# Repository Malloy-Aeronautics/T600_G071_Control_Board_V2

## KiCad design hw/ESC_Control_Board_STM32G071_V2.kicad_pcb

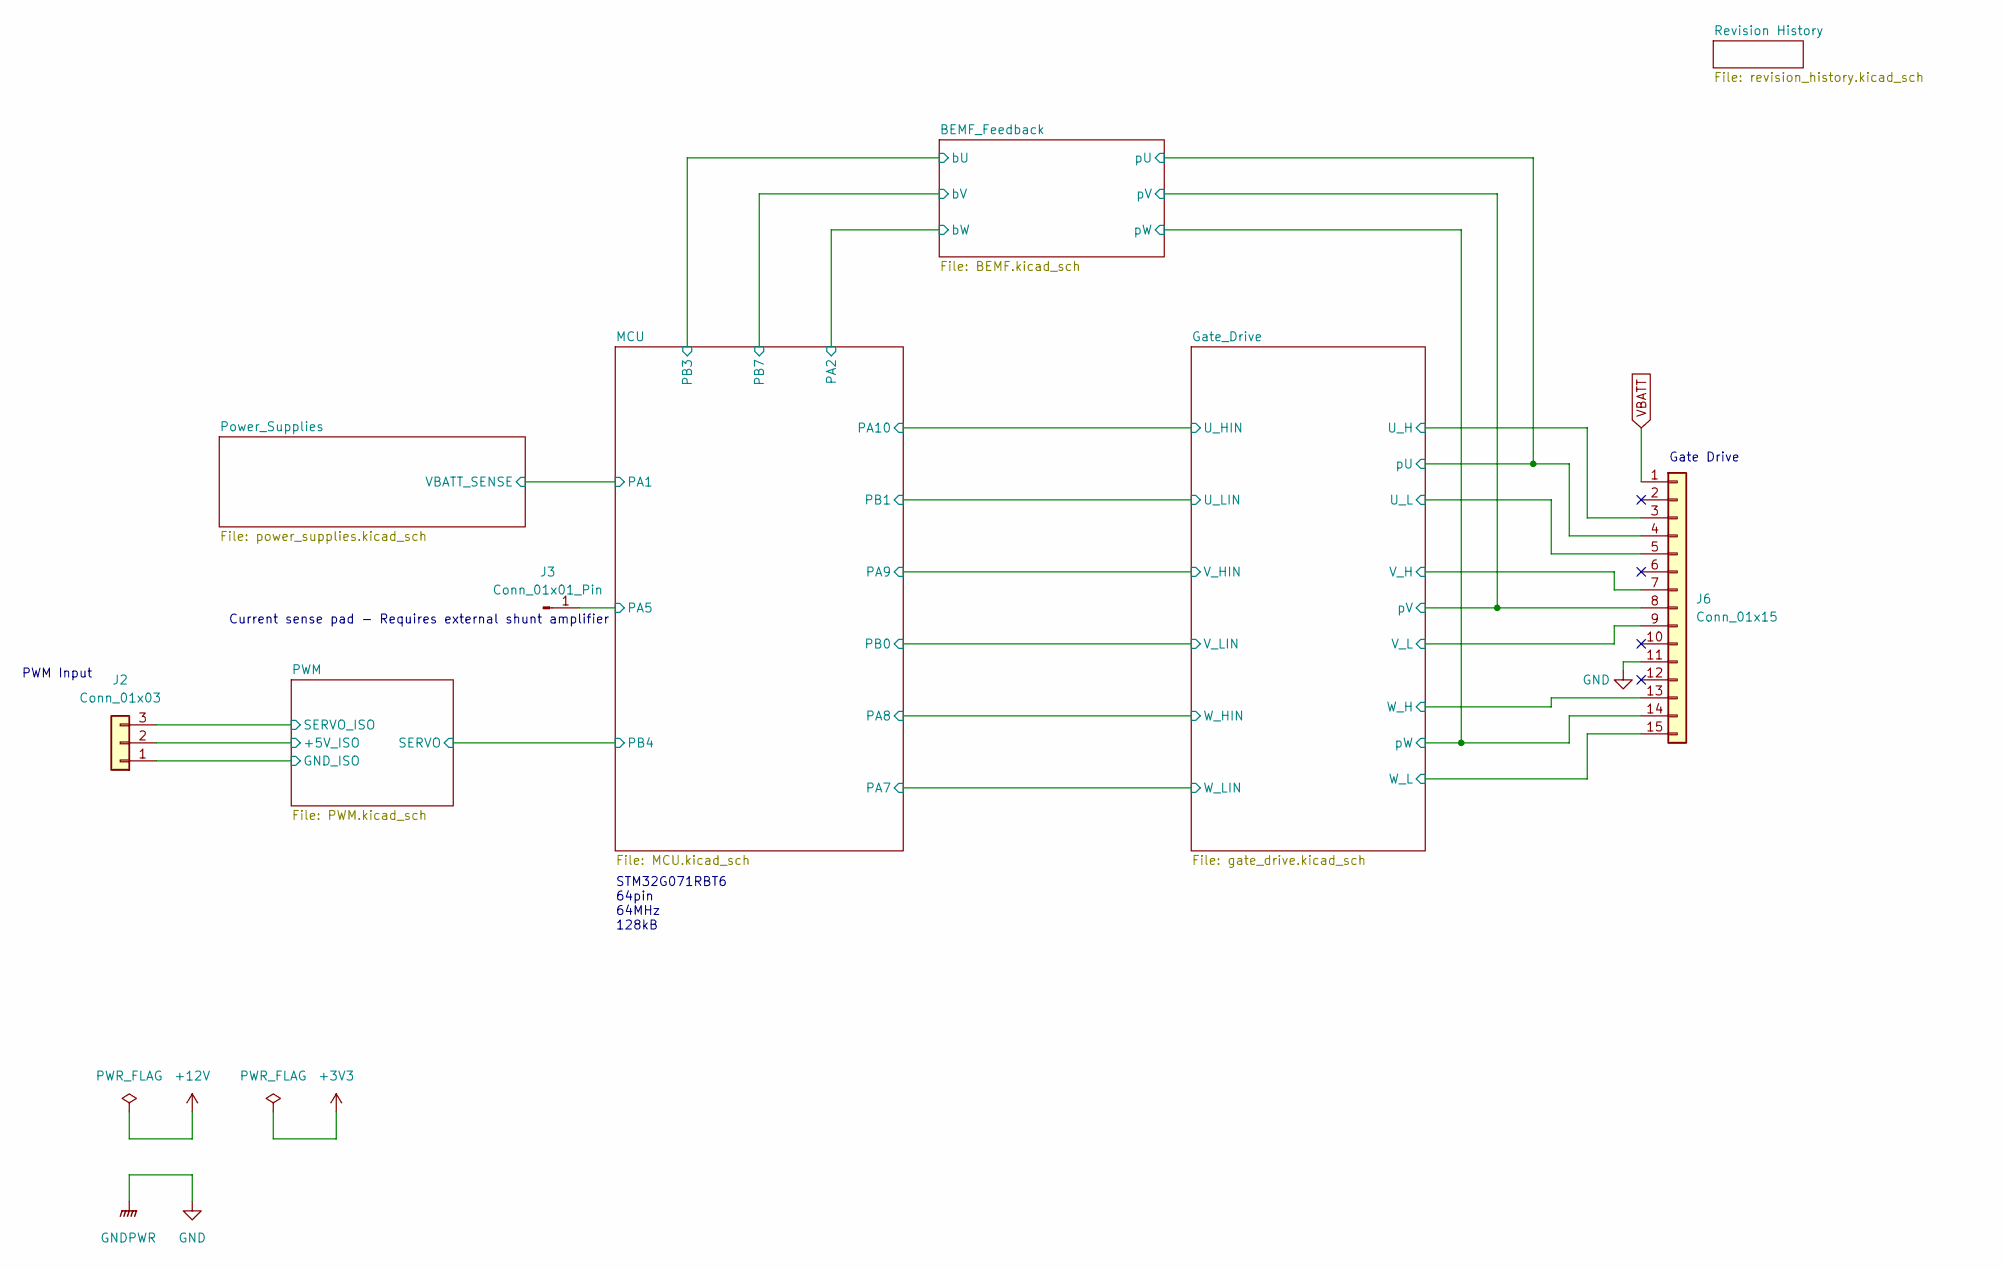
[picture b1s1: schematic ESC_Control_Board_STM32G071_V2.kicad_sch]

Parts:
J2: Conn_01x03; PWM_PADS
J3: Conn_01x01_Pin; TestPoint_Pad_1.0x1.0mm
J6: Conn_01x15; PinHeader_1x15_P2.00mm_Vertical

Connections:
/BEMF_Feedback/pU: J6.4; also elsewhere on the board
/BEMF_Feedback/pV: J6.8; also elsewhere on the board
/BEMF_Feedback/pW: J6.14; also elsewhere on the board
/Gate_Drive/U_H: J6.3; also elsewhere on the board
/Gate_Drive/U_L: J6.5; also elsewhere on the board
/Gate_Drive/V_H: J6.7; also elsewhere on the board
/Gate_Drive/V_L: J6.9; also elsewhere on the board
/Gate_Drive/W_H: J6.13; also elsewhere on the board
/Gate_Drive/W_L: J6.15; also elsewhere on the board
/MCU/PA5: J3.1; also elsewhere on the board
/PWM/+5V_ISO: J2.2; also elsewhere on the board
/PWM/GND_ISO: J2.1; also elsewhere on the board
/PWM/SERVO_ISO: J2.3; also elsewhere on the board
GND: J6.11; also elsewhere on the board
VBATT: J6.1; also elsewhere on the board

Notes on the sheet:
PWM Input
Gate Drive
STM32G071RBT6 64pin 64MHz 128kB
Current sense pad - Requires external shunt amplifier

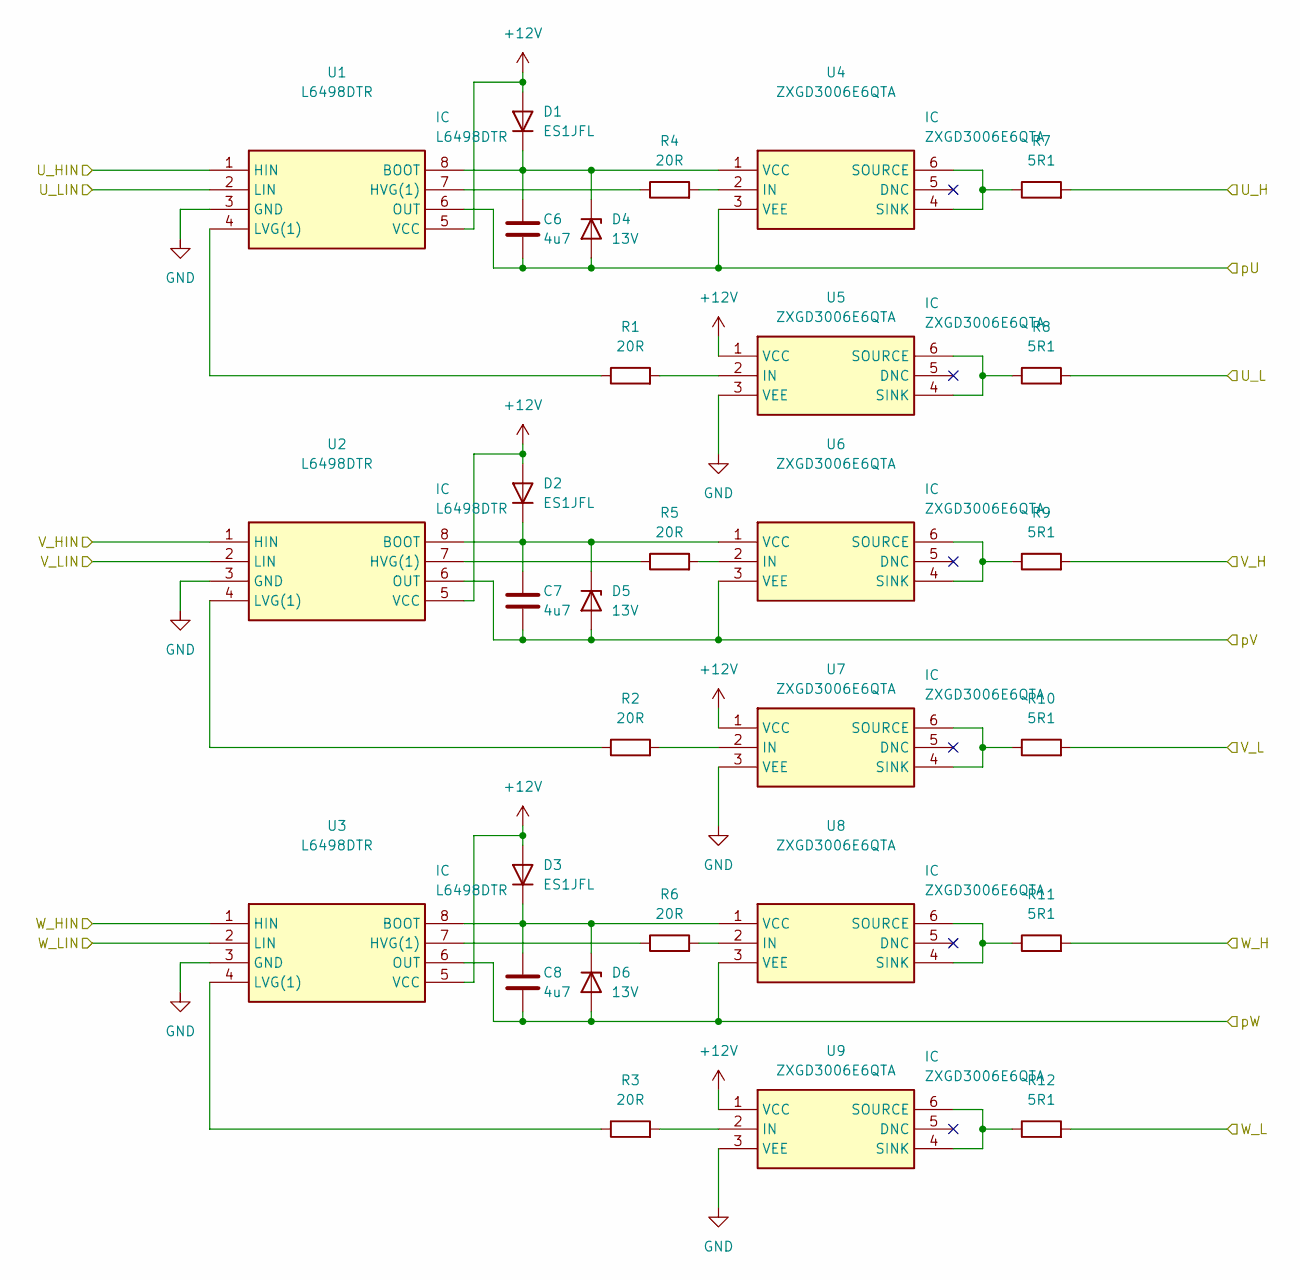
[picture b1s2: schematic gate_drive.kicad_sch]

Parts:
C6, C7, C8: 4u7; C_0603_1608Metric; Manufacturer_Part_Number GRT188C81E475KE13D
D1, D2, D3: ES1JFL; D_SOD-123F
D4, D5, D6: 13V; D_SOD-523
R1, R2, R3, R4, R5, R6: 20R; R_0603_1608Metric
R7, R8, R9, R10, R11, R12: 5R1; R_0805_2012Metric
U1, U2, U3: L6498DTR; SOT127P600X175-8N; Mouser Part Number 511-L6498DTR
U4, U5, U6, U7, U8, U9: ZXGD3006E6QTA; SOT95P285X140-6N; Mouser Part Number 621-ZXGD3006E6QTA

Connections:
+12V: D1.2 (A), D2.2 (A), D3.2 (A), U1.5 (VCC), U2.5 (VCC), U3.5 (VCC), U5.1 (VCC), U7.1 (VCC), U9.1 (VCC); also elsewhere on the board
/BEMF_Feedback/pU: C6.2, D4.2 (A), U1.6 (OUT), U4.3 (VEE); also elsewhere on the board
/BEMF_Feedback/pV: C7.2, D5.2 (A), U2.6 (OUT), U6.3 (VEE); also elsewhere on the board
/BEMF_Feedback/pW: C8.2, D6.2 (A), U3.6 (OUT), U8.3 (VEE); also elsewhere on the board
/Gate_Drive/U_H: R7.2; also elsewhere on the board
/Gate_Drive/U_HIN: U1.1 (HIN); also elsewhere on the board
/Gate_Drive/U_L: R8.2; also elsewhere on the board
/Gate_Drive/U_LIN: U1.2 (LIN); also elsewhere on the board
/Gate_Drive/V_H: R9.2; also elsewhere on the board
/Gate_Drive/V_HIN: U2.1 (HIN); also elsewhere on the board
/Gate_Drive/V_L: R10.2; also elsewhere on the board
/Gate_Drive/V_LIN: U2.2 (LIN); also elsewhere on the board
/Gate_Drive/W_H: R11.2; also elsewhere on the board
/Gate_Drive/W_HIN: U3.1 (HIN); also elsewhere on the board
/Gate_Drive/W_L: R12.2; also elsewhere on the board
/Gate_Drive/W_LIN: U3.2 (LIN); also elsewhere on the board
GND: U1.3 (GND), U2.3 (GND), U3.3 (GND), U5.3 (VEE), U7.3 (VEE), U9.3 (VEE); also elsewhere on the board
unnamed: C6.1, D1.1 (K), D4.1 (K), U1.8 (BOOT), U4.1 (VCC)
unnamed: C7.1, D2.1 (K), D5.1 (K), U2.8 (BOOT), U6.1 (VCC)
unnamed: C8.1, D3.1 (K), D6.1 (K), U3.8 (BOOT), U8.1 (VCC)
unnamed: R4.1, U1.7 (HVG(1))
unnamed: R1.1, U1.4 (LVG(1))
unnamed: R5.1, U2.7 (HVG(1))
unnamed: R2.1, U2.4 (LVG(1))
unnamed: R6.1, U3.7 (HVG(1))
unnamed: R3.1, U3.4 (LVG(1))
unnamed: R4.2, U4.2 (IN)
unnamed: R7.1, U4.4 (SINK), U4.6 (SOURCE)
unnamed: R1.2, U5.2 (IN)
unnamed: R8.1, U5.4 (SINK), U5.6 (SOURCE)
unnamed: R5.2, U6.2 (IN)
unnamed: R9.1, U6.4 (SINK), U6.6 (SOURCE)
unnamed: R2.2, U7.2 (IN)
unnamed: R10.1, U7.4 (SINK), U7.6 (SOURCE)
unnamed: R6.2, U8.2 (IN)
unnamed: R11.1, U8.4 (SINK), U8.6 (SOURCE)
unnamed: R3.2, U9.2 (IN)
unnamed: R12.1, U9.4 (SINK), U9.6 (SOURCE)

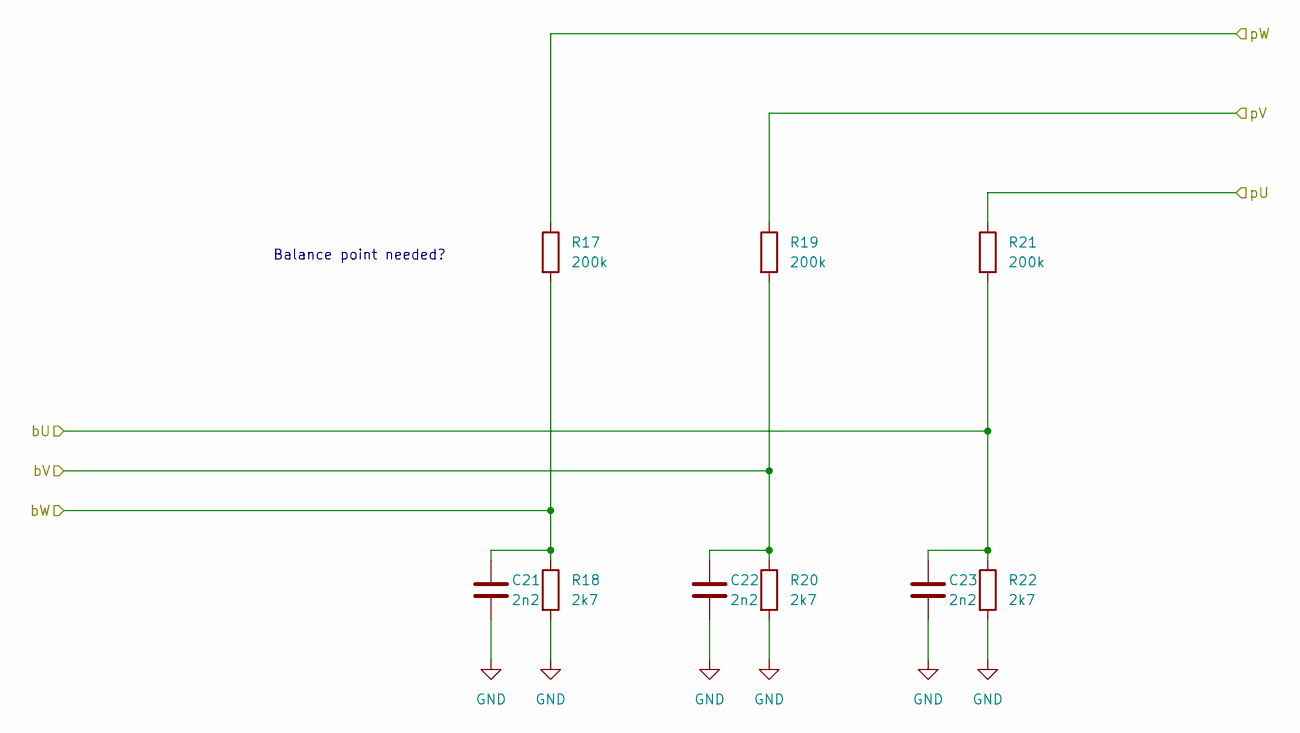
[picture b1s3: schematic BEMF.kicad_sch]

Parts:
C21, C22, C23: 2n2; C_0603_1608Metric
R17, R19, R21: 200k; R_0805_2012Metric
R18, R20, R22: 2k7; R_0603_1608Metric

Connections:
/BEMF_Feedback/bU: C23.1, R21.2, R22.1; also elsewhere on the board
/BEMF_Feedback/bV: C22.1, R19.2, R20.1; also elsewhere on the board
/BEMF_Feedback/bW: C21.1, R17.2, R18.1; also elsewhere on the board
/BEMF_Feedback/pU: R21.1; also elsewhere on the board
/BEMF_Feedback/pV: R19.1; also elsewhere on the board
/BEMF_Feedback/pW: R17.1; also elsewhere on the board
GND: C21.2, C22.2, C23.2, R18.2, R20.2, R22.2; also elsewhere on the board

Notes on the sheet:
Balance point needed?

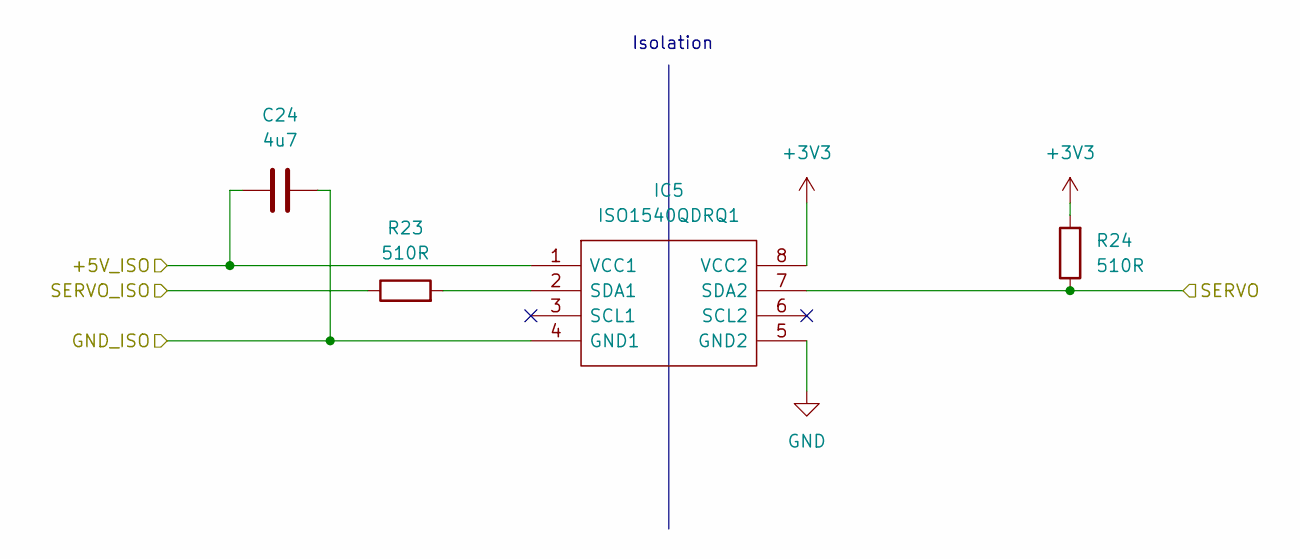
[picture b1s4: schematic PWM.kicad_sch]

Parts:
C24: 4u7; C_0603_1608Metric; Manufacturer_Part_Number GRT188C81E475KE13D
IC5: ISO1540QDRQ1; SOIC127P600X175-8N; Mouser Part Number 595-ISO1540QDRQ1
R23, R24: 510R; R_0603_1608Metric

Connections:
+3V3: IC5.8 (VCC2), R24.2; also elsewhere on the board
/MCU/PB4: IC5.7 (SDA2), R24.1; also elsewhere on the board
/PWM/+5V_ISO: C24.1, IC5.1 (VCC1); also elsewhere on the board
/PWM/GND_ISO: C24.2, IC5.4 (GND1); also elsewhere on the board
/PWM/SERVO_ISO: R23.1; also elsewhere on the board
GND: IC5.5 (GND2); also elsewhere on the board
unnamed: IC5.2 (SDA1), R23.2

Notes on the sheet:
Isolation

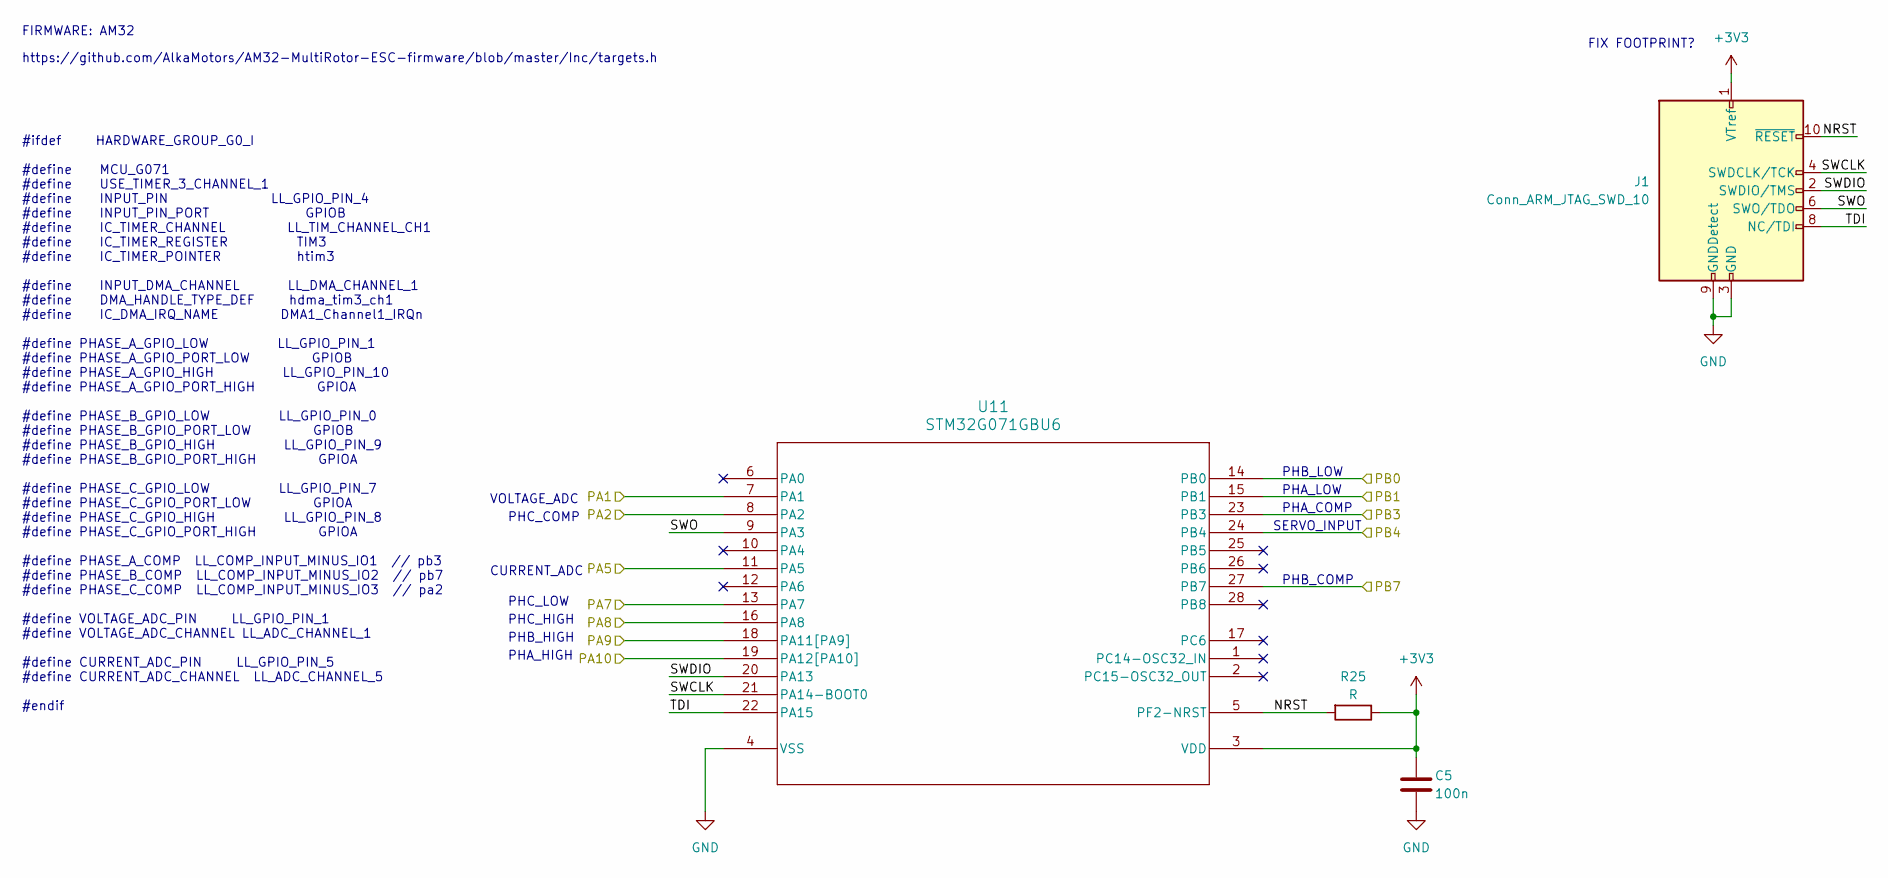
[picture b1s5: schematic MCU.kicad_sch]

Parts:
C5: 100n; C_0603_1608Metric
J1: Conn_ARM_JTAG_SWD_10; Tag-Connect_TC2050-IDC-NL_2x05_P1.27mm_Vertical_with_bottom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
R25: R
U11: STM32G071GBU6; UFQFPN-28

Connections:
+3V3: C5.1, J1.1 (VTref), R25.1, U11.3 (VDD); also elsewhere on the board
/BEMF_Feedback/bU: U11.23 (PB3); also elsewhere on the board
/BEMF_Feedback/bV: U11.27 (PB7); also elsewhere on the board
/BEMF_Feedback/bW: U11.8 (PA2); also elsewhere on the board
/Gate_Drive/U_HIN: U11.19 (PA12[PA10]); also elsewhere on the board
/Gate_Drive/U_LIN: U11.15 (PB1); also elsewhere on the board
/Gate_Drive/V_HIN: U11.18 (PA11[PA9]); also elsewhere on the board
/Gate_Drive/V_LIN: U11.14 (PB0); also elsewhere on the board
/Gate_Drive/W_HIN: U11.16 (PA8); also elsewhere on the board
/Gate_Drive/W_LIN: U11.13 (PA7); also elsewhere on the board
/MCU/NRST: J1.10 (~RESET), R25.2, U11.5 (PF2-NRST)
/MCU/PA1: U11.7 (PA1); also elsewhere on the board
/MCU/PA5: U11.11 (PA5); also elsewhere on the board
/MCU/PB4: U11.24 (PB4); also elsewhere on the board
/MCU/SWCLK: J1.4 (SWDCLK/TCK), U11.21 (PA14-BOOT0)
/MCU/SWDIO: J1.2 (SWDIO/TMS), U11.20 (PA13)
/MCU/SWO: J1.6 (SWO/TDO), U11.9 (PA3)
/MCU/TDI: J1.8 (NC/TDI), U11.22 (PA15)
GND: C5.2, J1.3 (GND), J1.5 (GND), J1.9 (GNDDetect), U11.4 (VSS); also elsewhere on the board

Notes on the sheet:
PHB_COMP
https://github.com/AlkaMotors/AM32-MultiRotor-ESC-firmware/blob/master/Inc/targets.h
CURRENT_ADC
FIRMWARE: AM32
PHC_HIGH
SERVO_INPUT
PHB_LOW
PHA_LOW
FIX FOOTPRINT?
PHC_COMP
PHA_COMP
PHC_LOW
PHB_HIGH
VOLTAGE_ADC
PHA_HIGH
#ifdef HARDWARE_GROUP_G0_I #define MCU_G071 #define USE_TIMER_3_CHANNEL_1 #define INPUT_PIN LL_GPIO_PIN_4 #define INPUT_PIN_PORT GPIOB #define IC_TIMER_CHANNEL LL_TIM_CHANNEL_CH1 #define IC_TIMER_REGISTER TIM3 #define IC_TIMER_POINTER htim3 #define INPUT_DMA_CHANNEL LL_DMA_CHANNEL_1 #define DMA_HAN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

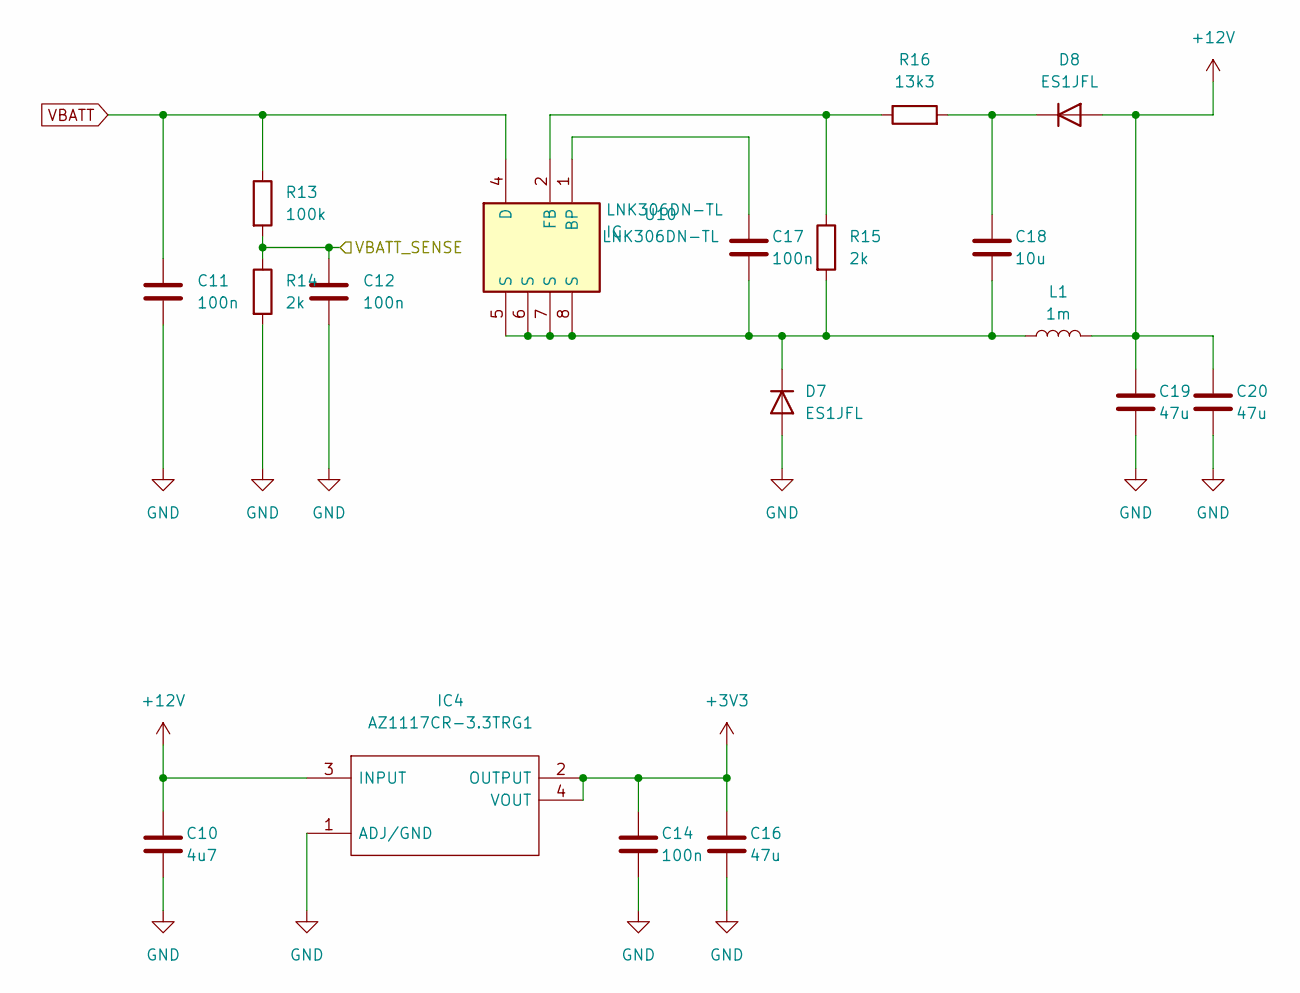
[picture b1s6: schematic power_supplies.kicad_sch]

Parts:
C10: 4u7; C_0603_1608Metric; Manufacturer_Part_Number GRT188C81E475KE13D
C11: 100n; C_0805_2012Metric
C12, C14, C17: 100n; C_0603_1608Metric
C16, C19, C20: 47u; C_1210_3225Metric
C18: 10u; C_0603_1608Metric
D7, D8: ES1JFL; D_SOD-123F
IC4: AZ1117CR-3.3TRG1; AZ1117CR33TRG1; Mouser Part Number 621-AZ1117CR-3.3TRG1
L1: 1m; L_7.3x7.3_H4.5
R13: 100k; R_0805_2012Metric
R14, R15: 2k; R_0603_1608Metric
R16: 13k3; R_0603_1608Metric
U10: LNK306DN-TL; SOIC127P600X175-8N_MISSING_PIN; Mouser Part Number 869-LNK306DN-TL

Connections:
+3V3: C14.1, C16.1, IC4.2 (OUTPUT), IC4.4 (VOUT); also elsewhere on the board
+12V: C10.1, C19.1, C20.1, D8.2 (A), IC4.3 (INPUT), L1.2; also elsewhere on the board
/MCU/PA1: C12.1, R13.2, R14.1; also elsewhere on the board
GND: C10.2, C11.2, C12.2, C14.2, C16.2, C19.2, C20.2, D7.2 (A), IC4.1 (ADJ/GND), R14.2; also elsewhere on the board
unnamed: C17.2, C18.2, D7.1 (K), L1.1, R15.2, U10.5 (S), U10.6 (S), U10.7 (S), U10.8 (S)
unnamed: C18.1, D8.1 (K), R16.2
unnamed: C17.1, U10.1 (BP)
unnamed: R15.1, R16.1, U10.2 (FB)
VBATT: C11.1, R13.1, U10.4 (D); also elsewhere on the board

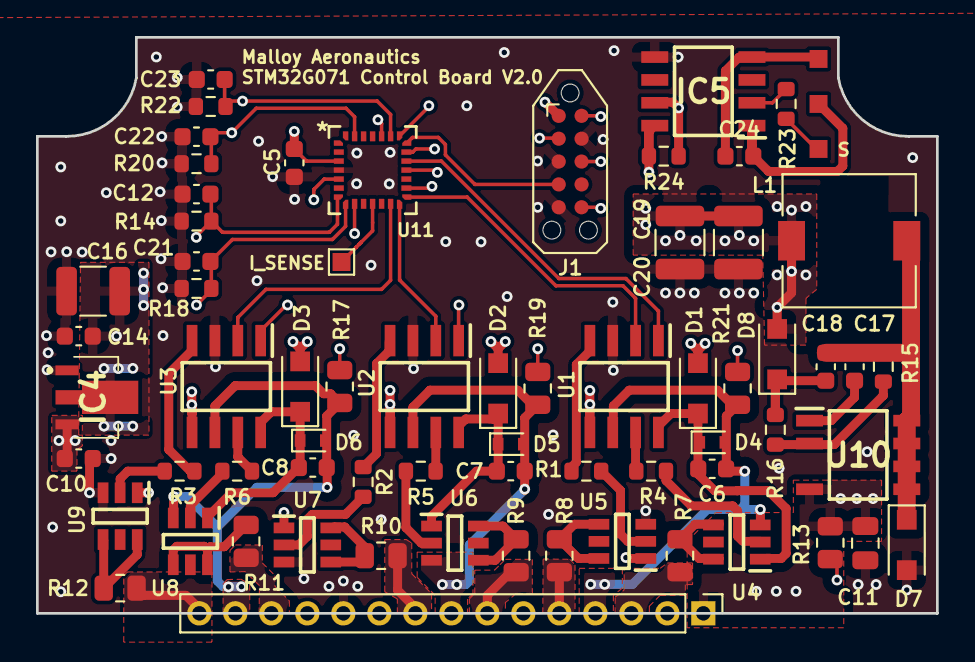
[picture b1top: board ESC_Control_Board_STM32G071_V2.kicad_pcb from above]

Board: 6 copper layers, 50.0 x 32.0 mm, 67 parts (0 on the bottom side), 59 nets.

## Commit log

2023-05-23 Added ma_kicad_library as submodule
2023-05-23 Updated submodule version for kicad library
2023-06-05 Layout updates
2023-06-05 Renamed gate-drive sheet
2023-06-09 Updates for review
2023-06-09 added hw folder
2023-06-09 removed submodule
2023-06-09 readded submodule
2023-06-09 added doc and images folders
2023-06-09 connected interrupt pins to CAN controller
2023-06-20 Revision V1.0
2023-06-20 Added gerbers
2023-08-16 update comments
2023-08-24 commenting
